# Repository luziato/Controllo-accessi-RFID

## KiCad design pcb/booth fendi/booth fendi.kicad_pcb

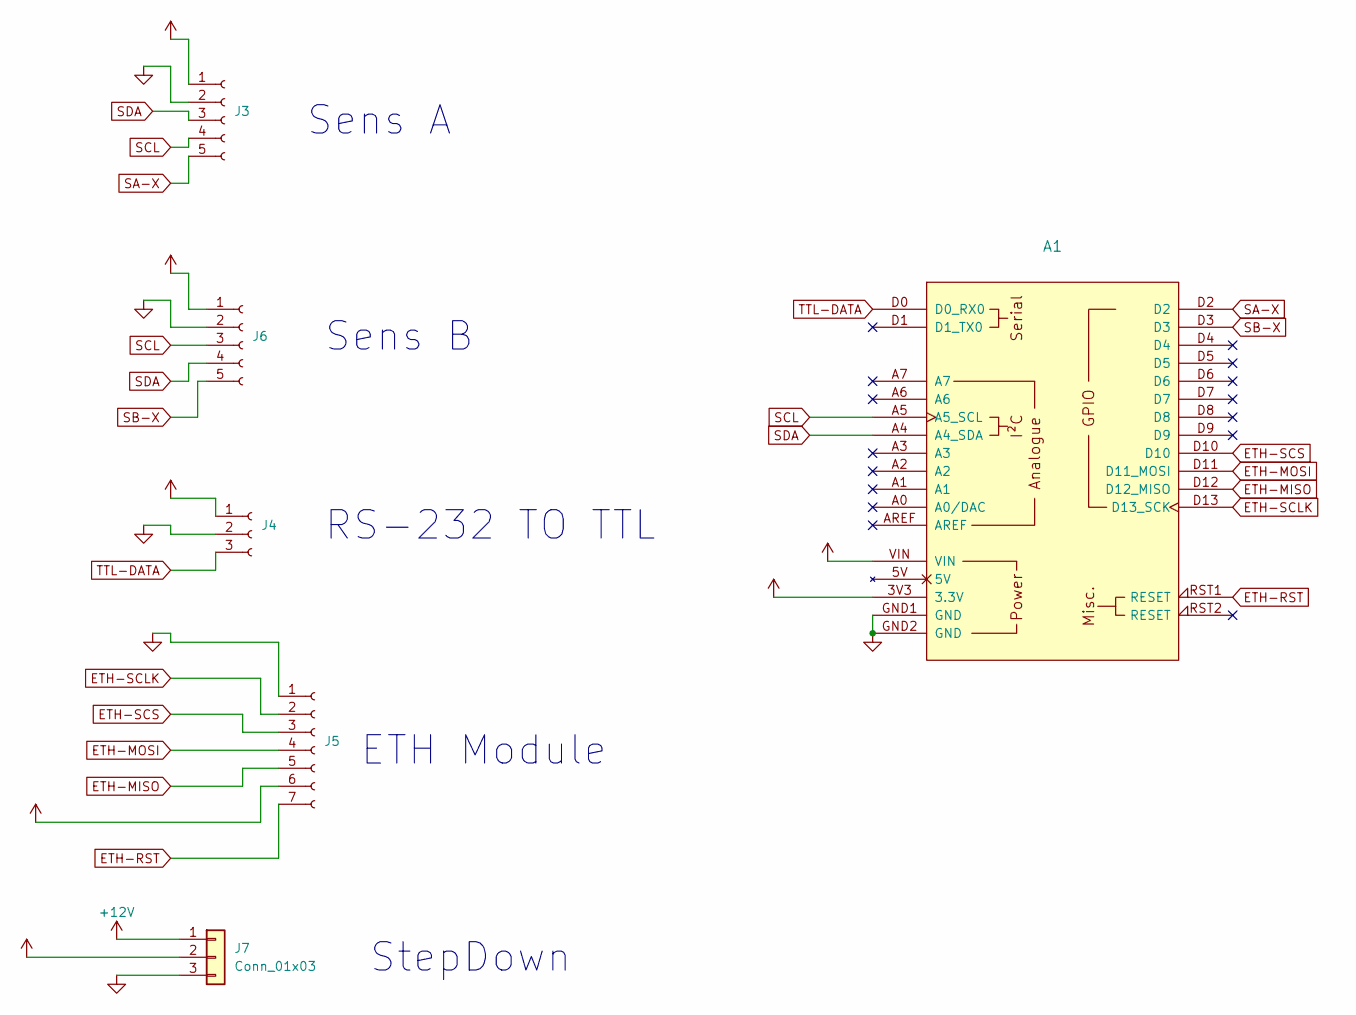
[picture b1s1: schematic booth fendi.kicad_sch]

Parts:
A1: Arduino_Nano_33_IoT_Tile; Arduino_Nano_33_IoT_Socket
J3, J6: Conn_01x05_Female; SolderWire-0.75sqmm_1x05_P4.8mm_D1.25mm_OD2.3mm
J4: Conn_01x03_Female; SolderWire-0.75sqmm_1x03_P4.8mm_D1.25mm_OD2.3mm
J5: Conn_01x07_Female; SolderWire-1.5sqmm_1x07_P6mm_D1.7mm_OD3mm
J7: Conn_01x03; SolderWire-0.75sqmm_1x03_P4.8mm_D1.25mm_OD2.3mm

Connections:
+3V3: A1.3V3 (3.3V), J3.1, J4.1, J5.6, J6.1
+5V: A1.VIN, J7.2; also elsewhere on the board
+12V: J7.1; also elsewhere on the board
ETH-MISO: A1.D12 (D12_MISO), J5.5
ETH-MOSI: A1.D11 (D11_MOSI), J5.4
ETH-RST: A1.RST1 (RESET), J5.7
ETH-SCLK: A1.D13 (D13_SCK), J5.2
ETH-SCS: A1.D10, J5.3
GND: A1.GND1 (GND), A1.GND2 (GND), J3.2, J4.2, J5.1, J6.2, J7.3; also elsewhere on the board
SA-X: A1.D2, J3.5
SB-X: A1.D3, J6.5
SCL: A1.A5 (A5_SCL), J3.4, J6.3
SDA: A1.A4 (A4_SDA), J3.3, J6.4
TTL-DATA: A1.D0 (D0_RX0), J4.3

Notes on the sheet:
Sens B
Sens A
RS-232 TO TTL
StepDown
ETH Module

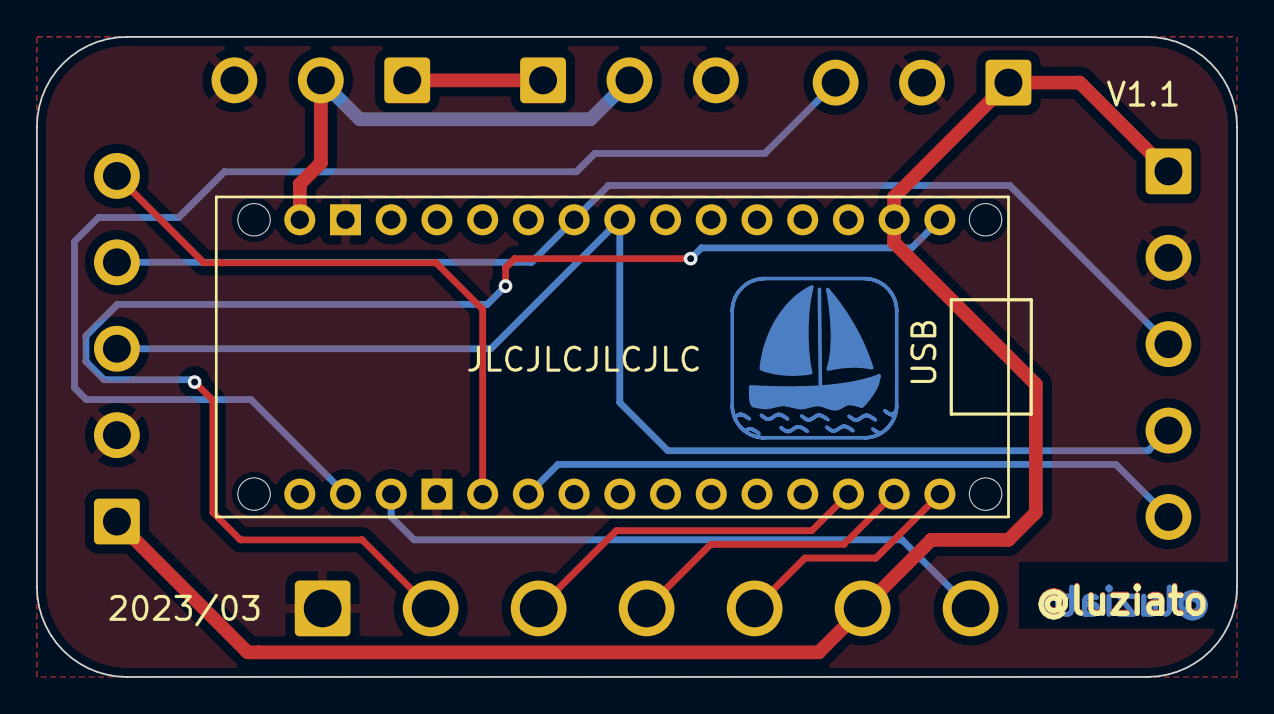
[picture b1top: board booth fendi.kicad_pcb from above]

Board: 2 copper layers, 66.7 x 35.6 mm, 7 parts (0 on the bottom side), 14 nets.

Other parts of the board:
J2: Conn_01x03_Female; SolderWire-0.75sqmm_1x03_P4.8mm_D1.25mm_OD2.3mm

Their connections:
+5V: J2.2; also elsewhere on the board
+12V: J2.1; also elsewhere on the board
GND: J2.3; also elsewhere on the board

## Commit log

2023-03-06 Tracing GND
    Traced GND on the PCB
2023-03-06 traced no silkscreen
2023-03-06 Geerated gerber and added to Gerber.zip
2023-03-06 nuovo codice stabile con MQTT
2023-03-06 mooved to old dir
2023-03-06 Retraced, need the silkscreen
2023-03-06 Moved to old dir
2023-03-06 Completed, To be reviewed DRC errors
2023-03-07 To be reviewed drc errors
2023-03-08 Reviewed DRC, added logo, ready to be quoted
2023-03-08 Exported .Gerber file and zipped
2023-03-08 Tolerances for JLCPCB, Reordered silk
    modified tolerances for JLCPCB accomodations, moved veriosn number and date and added "JLC.." order number under the arduino.
2023-03-08 Reviewed DRC, sent to production to JLC, generated Gerber
